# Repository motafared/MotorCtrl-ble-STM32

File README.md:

# MotorCtrl BLE — STM32WB55 Dual BLDC Motor Controller (Phase 2)

Wireless control and live telemetry for a **dual 12 V BLDC motor controller**, built on the
**WeAct STM32WB55** (Cortex-M4 + Bluetooth LE 5.0). Phase 2 adds BLE control plus a
**Web Bluetooth dashboard** — drive the motors and watch live data from a phone or laptop, with
no app install. The original push-button control still works in parallel.

> 🌐 **Live dashboard:** **https://motafared.github.io/MotorCtrl-ble-STM32/** — open in
> Chrome / Edge on desktop or Android (no install). Needs Bluetooth on; Android also needs
> Location enabled for BLE scanning.
>
> 📄 **Full delivery document:** [`docs/phase2_delivery.md`](docs/phase2_delivery.md)
> ([styled HTML](docs/phase2_delivery.html)) — scope, BOM, wiring, flashing, GATT reference,
> dashboard usage, troubleshooting.

## Repository layout (monorepo)

```
Phase2-Project/
├── firmware/   STM32WB55 application (STM32CubeIDE) + BLE GATT services
├── WebApp/     Web Bluetooth dashboard (single-page, no install)
├── kicad/      Hardware design (KiCad, generated from SKiDL)
└── docs/       Delivery doc + connection diagrams
```

## At a glance

- **Two BLDC motors**, closed-loop PID speed control (100 ms tick), tachometer feedback.
- **Three run modes:** Timed run (default 35 s) · Continuous (CONTINUE button: run while held; app command: latched until Stop) · Stopped.
- **Live telemetry:** actual speed, cumulative rotations, elapsed time, and run state.
- **Buttons + BLE in parallel** — the dashboard tracks physical button presses live.

## Hardware

| Item | Detail |
|---|---|
| MCU | WeAct STM32WB55 Core Board (STM32WB55CGU6, 64 MHz, BLE 5.0) |
| Motors | 2× BLDC 12 V 4-wire |
| PWM | PA0 (M1) / PA1 (M2) — TIM2, 20 kHz |
| Tachometer | PA8 (M1) / PA9 (M2) — TIM1 input capture |
| PID tick | TIM16 — 100 ms |
| Buttons | PA2 STOP, PA3 START, PA4 CONTINUE — EXTI, **active-HIGH, internal pull-down** |
| Status LED | PE4 (blue) — ON running, 5 Hz heartbeat |

## BLE GATT

Advertised name **`MotorCtrl`**. All multi-byte values little-endian.

**Control service `0x0001`**

| Char | UUID | Type | Access | Meaning |
|---|---|---|---|---|
| TSM1 | 0x0002 | u16 | R/W | Target speed M1 (RPM) |
| TSM2 | 0x0003 | u16 | R/W | Target speed M2 (RPM) |
| CT | 0x0004 | u16 | R/W | Cycle time (s) |
| CMD | 0x0005 | u8 | W | `0x01` start timed · `0x02` stop · `0x03` start continuous |

**Telemetry service `0x0010`** (Read / Notify)

| Char | UUID | Type | Meaning |
|---|---|---|---|
| ASM1 / ASM2 | 0x0011 / 0x0012 | u16 | Actual speed M1 / M2 (RPM) |
| RM1 / RM2 | 0x0013 / 0x0014 | u32 | Cumulative rotations M1 / M2 |
| ET | 0x0015 | u16 | Elapsed time (s) |
| STATUS | 0x0016 | u8 | Run state: `0` idle · `1` timed · `2` continuous |

Reads return live values (refreshed from firmware state on each read). STATUS is notified on
every transition — BLE command, timed auto-stop, **and** physical button presses.

## Build & flash (firmware)

This project is **STM32CubeIDE only**.

1. **One-time:** flash the CPU2 BLE stack with STM32CubeProgrammer — `stm32wb5x_FUS_fw.bin` at
   `0x080EC000` (skip if FUS ≥ 1.2.0), then `stm32wb5x_BLE_Stack_full_fw.bin` at `0x080C0000`.
2. Open `firmware/` in STM32CubeIDE → **Build All** → **Run** to flash the application.

**Build modes** — one switch in `firmware/Core/Inc/main.h`:

| `MOTOR_MODE` | Tacho PPR | PWM polarity | Use |
|---|---|---|---|
| `MODE_KHALED` | 2 | non-inverted | bench testing |
| `MODE_TOON` | 6 | inverted | client hardware |

Defaults: target 1200 RPM/motor, 35 s cycle, PID `Kp = 0.012`.

## Run the dashboard

**Hosted (no install):** open **https://motafared.github.io/MotorCtrl-ble-STM32/** in Chrome / Edge.

Or serve it locally:

```bash
cd WebApp
python -m http.server 8000      # then open http://localhost:8000 in Chrome
```

- **Browsers:** Chrome / Edge / Brave (desktop, Android); **Bluefy** on iOS.
- Web Bluetooth needs a secure context (`https://` or `http://localhost`); `file://` won't work.
- After flashing new firmware, **hard-reload** the page (Ctrl+Shift+R) to avoid a cached script.

## License

Proprietary — all rights reserved. Client project for Toon.

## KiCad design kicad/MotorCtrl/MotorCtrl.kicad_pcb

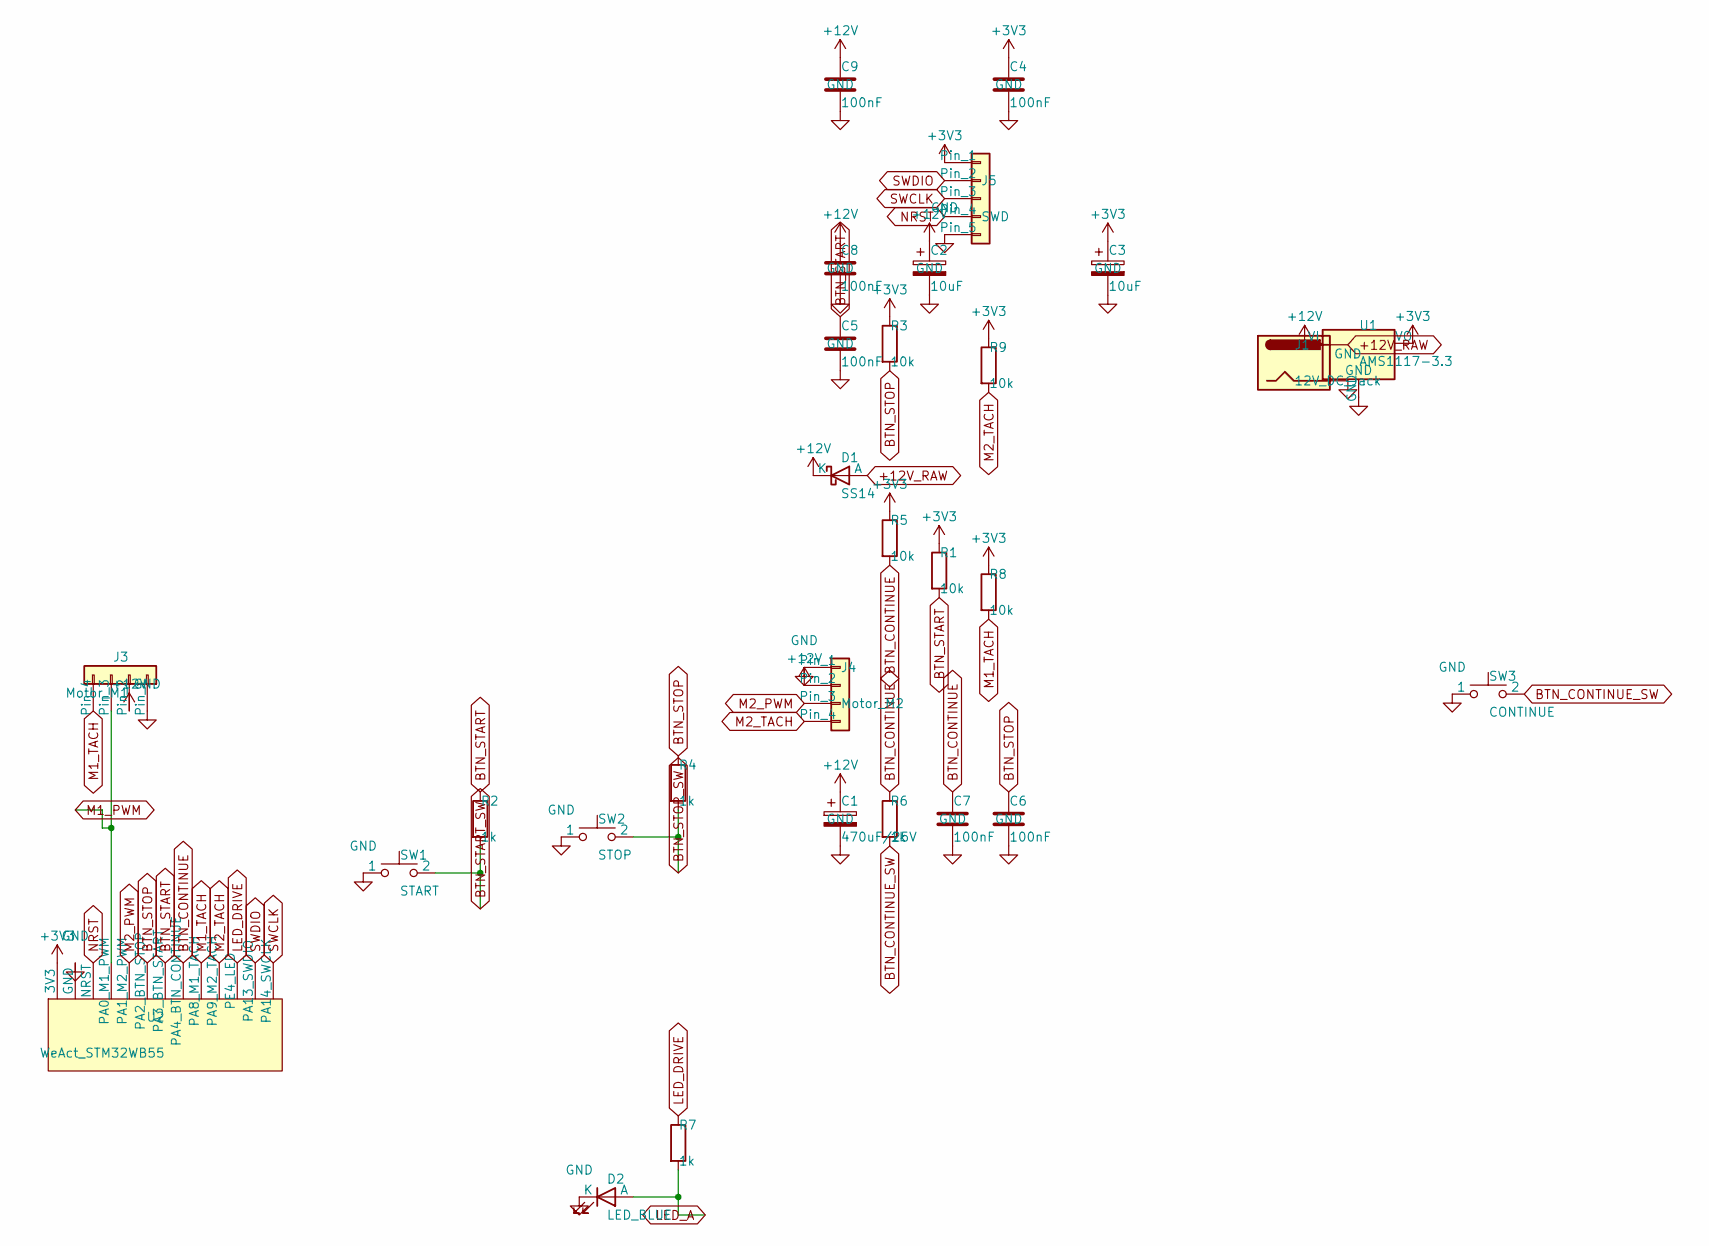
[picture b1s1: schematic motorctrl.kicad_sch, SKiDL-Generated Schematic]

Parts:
C1: 470uF/25V; CP_Radial_D8.0mm_P3.50mm
C2, C3: 10uF; CP_Elec_5x5.4
C4, C5, C6, C7, C8, C9: 100nF; C_0805_2012Metric
D1: SS14; D_SMA
D2: LED_BLUE; LED_0805_2012Metric
J1: 12V_DC_Jack; BarrelJack_Horizontal
J3: Motor_M1; PinHeader_1x04_P2.54mm_Vertical
J4: Motor_M2; PinHeader_1x04_P2.54mm_Vertical
J5: SWD; PinHeader_1x05_P2.54mm_Vertical
R1, R3, R5, R8, R9: 10k; R_0805_2012Metric
R2, R4, R6, R7: 1k; R_0805_2012Metric
SW1: START; SW_PUSH_6mm
SW2: STOP; SW_PUSH_6mm
SW3: CONTINUE; SW_PUSH_6mm
U1: AMS1117-3.3; SOT-223-3_TabPin2
U2: WeAct_STM32WB55; PinHeader_2x12_P2.54mm_Vertical

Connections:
+3V3: C3.1, C4.1, J5.1, R1.1, R3.1, R5.1, R8.1, R9.1, U1.2 (VO), U2.1 (3V3)
+12V: C1.1, C2.1, C8.1, C9.1, D1.1 (K), J3.2, J4.2, U1.3 (VI)
+12V_RAW: D1.2 (A), J1.1
BTN_CONTINUE: C7.1, R5.2, R6.1, U2.8 (PA4_BTN_CONTINUE)
BTN_CONTINUE_SW: R6.2, SW3.2
BTN_START: C5.1, R1.2, R2.1, U2.7 (PA3_BTN_START)
BTN_START_SW: R2.2, SW1.2
BTN_STOP: C6.1, R3.2, R4.1, U2.6 (PA2_BTN_STOP)
BTN_STOP_SW: R4.2, SW2.2
GND: C1.2, C2.2, C3.2, C4.2, C5.2, C6.2, C7.2, C8.2, C9.2, D2.1 (K), J1.2, J3.1, J4.1, J5.5, SW1.1, SW2.1, SW3.1, U1.1 (GND), U2.2 (GND)
LED_A: D2.2 (A), R7.2
LED_DRIVE: R7.1, U2.11 (PE4_LED)
M1_PWM: J3.3, U2.4 (PA0_M1_PWM)
M1_TACH: J3.4, R8.2, U2.9 (PA8_M1_TACH)
M2_PWM: J4.3, U2.5 (PA1_M2_PWM)
M2_TACH: J4.4, R9.2, U2.10 (PA9_M2_TACH)
NRST: J5.4, U2.3 (NRST)
SWCLK: J5.3, U2.13 (PA14_SWCLK)
SWDIO: J5.2, U2.12 (PA13_SWDIO)

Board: 2 copper layers, 29 parts (0 on the bottom side), 19 nets, no tracks yet.

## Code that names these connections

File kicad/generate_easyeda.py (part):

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netlabel(798, 418, "+3V3")          # pin1
netlabel(798, 438, "GND")           # pin2
netlabel(798, 458, "NRST")          # pin3
netlabel(798, 478, "M1_PWM")        # pin4  PA0
netlabel(798, 498, "M2_PWM")        # pin5  PA1
netlabel(798, 518, "BTN_STOP")      # pin6  PA2
netlabel(798, 538, "BTN_START")     # pin7  PA3

# J2B — right pin row  (PA4, PA8, PA9, PE4, PA13, PA14)
# LCSC C124377  6-pin 2.54 mm single-row male header
comp(1010, 460, 0, "HDR-TH_6P-P2.54-V-M", "C124377", "J2B", "WB55_RIGHT")
netlabel(1042, 428, "BTN_CONTINUE") # pin1  PA4
netlabel(1042, 448, "M1_TACH")      # pin2  PA8
netlabel(1042, 468, "M2_TACH")      # pin3  PA9
netlabel(1042, 488, "LED_DRIVE")    # pin4  PE4
netlabel(1042, 508, "SWDIO")        # pin5  PA13
netlabel(1042, 528, "SWCLK")        # pin6  PA14

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# LCSC C25804
comp(1180, 170, 90, "R0402", "C25804", "R1", "10k")
netlabel(1180, 140, "+3V3")
netlabel(1180, 200, "M1_TACH")

# R2 — M2 tacho pull-up 10 kΩ
comp(1280, 170, 90, "R0402", "C25804", "R2", "10k")
netlabel(1280, 140, "+3V3")
netlabel(1280, 200, "M2_TACH")

# C2 — M1 motor power decoupling 100 nF
comp(1150, 340, 0, "C0402", "C1525", "C2", "100nF")
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netlabel(1260, 372, "GND")

# J3 — Motor M1 connector  KF2510 4-pin
# Pin order: 1=GND, 2=+12V, 3=M1_PWM, 4=M1_TACH
# LCSC C225517
comp(1520, 230, 0, "KF2510-4P", "C225517", "J3", "M1_CONN")
netlabel(1552, 208, "GND")
netlabel(1552, 224, "+12V")
netlabel(1552, 240, "M1_PWM")
netlabel(1552, 256, "M1_TACH")

# J4 — Motor M2 connector  KF2510 4-pin
comp(1520, 430, 0, "KF2510-4P", "C225517", "J4", "M2_CONN")
netlabel(1552, 408, "GND")
netlabel(1552, 424, "+12V")
netlabel(1552, 440, "M2_PWM")
netlabel(1552, 456, "M2_TACH")


# ─────────────────────────────────────────────────────────────
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
# R9 — 220 Ω series resistor (vertical: MCU → LED anode)
comp(1120, 760, 90, "R0402", "C25804", "R9", "220R")
netlabel(1120, 732, "LED_DRIVE")
netlabel(1120, 788, "LED_A")

# D2 — Blue 3 mm LED
# LCSC C84256   pin2=Anode(+) left   pin1=Cathode(-) right
comp(1260, 760, 0, "LED-TH_BD3.0-P2.54-FD", "C84256", "D2", "LED_BLUE")
netlabel(1228, 760, "LED_A")
netlabel(1292, 760, "GND")


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
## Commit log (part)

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2026-05-02 Add readable timer aliases to main.h (htim_tacho/htim_pwm/htim_pid)
